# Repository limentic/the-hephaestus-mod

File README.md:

# The Hephaestus Mod

## ⚠️ DISCLAIMER ⚠️
Magic Keyboard is a trademark of Apple Inc.\
Apple Magic Keyboard is a trademark of Apple Inc.\
Touch ID is a trademark of Apple Inc.\
This project is not affiliated with Apple Inc. in any way.

The Hephaestus Mod is an independent project created by hardware enthusiasts. It is not endorsed, sponsored, ore supported by Apple Inc. Use this project at your own risk. Modifying your Magic Keyboard WILL void any warranty provided by Apple Inc.

## Introduction
The Hephaestus Mod is an open-source hardware modification for the Apple Magic Keyboard. This project aims create a mechanical keyboard using the Apple Magic Keyboard as a base.

## Getting Started
The Hephaestus Mod project is organized into the following directories:
- `ECAD-files/` - Contains the KiCad project files for the Hephaestus Mod.
    In this directory, you will find the following subdirectories:
    - `dev-board/` - Contains the KiCad project files for the development board. This board was used to test out if the reverse engineered keyboard matrix was correct.
    It can also be repurposed as a breakout board for the matrix connector. \
    **Be careful!** The revision 1.0 of the board contains errors for the 9, TAB and Option Right keys. I will make another revision of the dev board when I have time.
    - `prod-board/` - Contains the KiCad project files for the production board. This board is the version of the Hephaestus Mod that is intended to be used. \
    **Be careful!** For the moment this board is still not tested. It is still in manufacturing. I will update this README when I have tested it and confirmed that it works.
    - `touch-id-ribbon` - Contains the KiCad project files for the Touch ID ribbon cable. This cable is used to connect the Touch ID connector on the Apple motherboard to the production board.
- `MCAD-files/` - Contains the .STEP files of the Hephaestus Mod.
    - `hephaestus-case.step` - The case for the Hephaestus Mod.
    - `hephaestus-main-board.step` - The 3D model of the production board.
    - `magic-keyboard-battery.step` - The 3D model of the Magic Keyboard battery.
    - `magic-keyboard-motherboard.step` - The 3D model of the Magic Keyboard motherboard.

## Presumed Keyboard Matrices
You can check the presumed keyboard matrices below :
- [AZERTY Keyboard Matrix](./matrices/AZERTY.md)

## Build Instructions
🚧 **This section will be updated with instructions on how to get started with the Hephaestus Mod when the project is considered done.** 🚧

## License
This project is licensed under the CERN-OHL-S. See the [LICENSE](LICENSE) file for details.

## Contributing
We welcome contributions! Please read our [contributing guidelines](CONTRIBUTING.md) for more information on how to get involved.

## Contact
For questions, issues, or suggestions, please open an issue on our [GitHub repository](https://github.com/limentic/the-hephaestus-mod).

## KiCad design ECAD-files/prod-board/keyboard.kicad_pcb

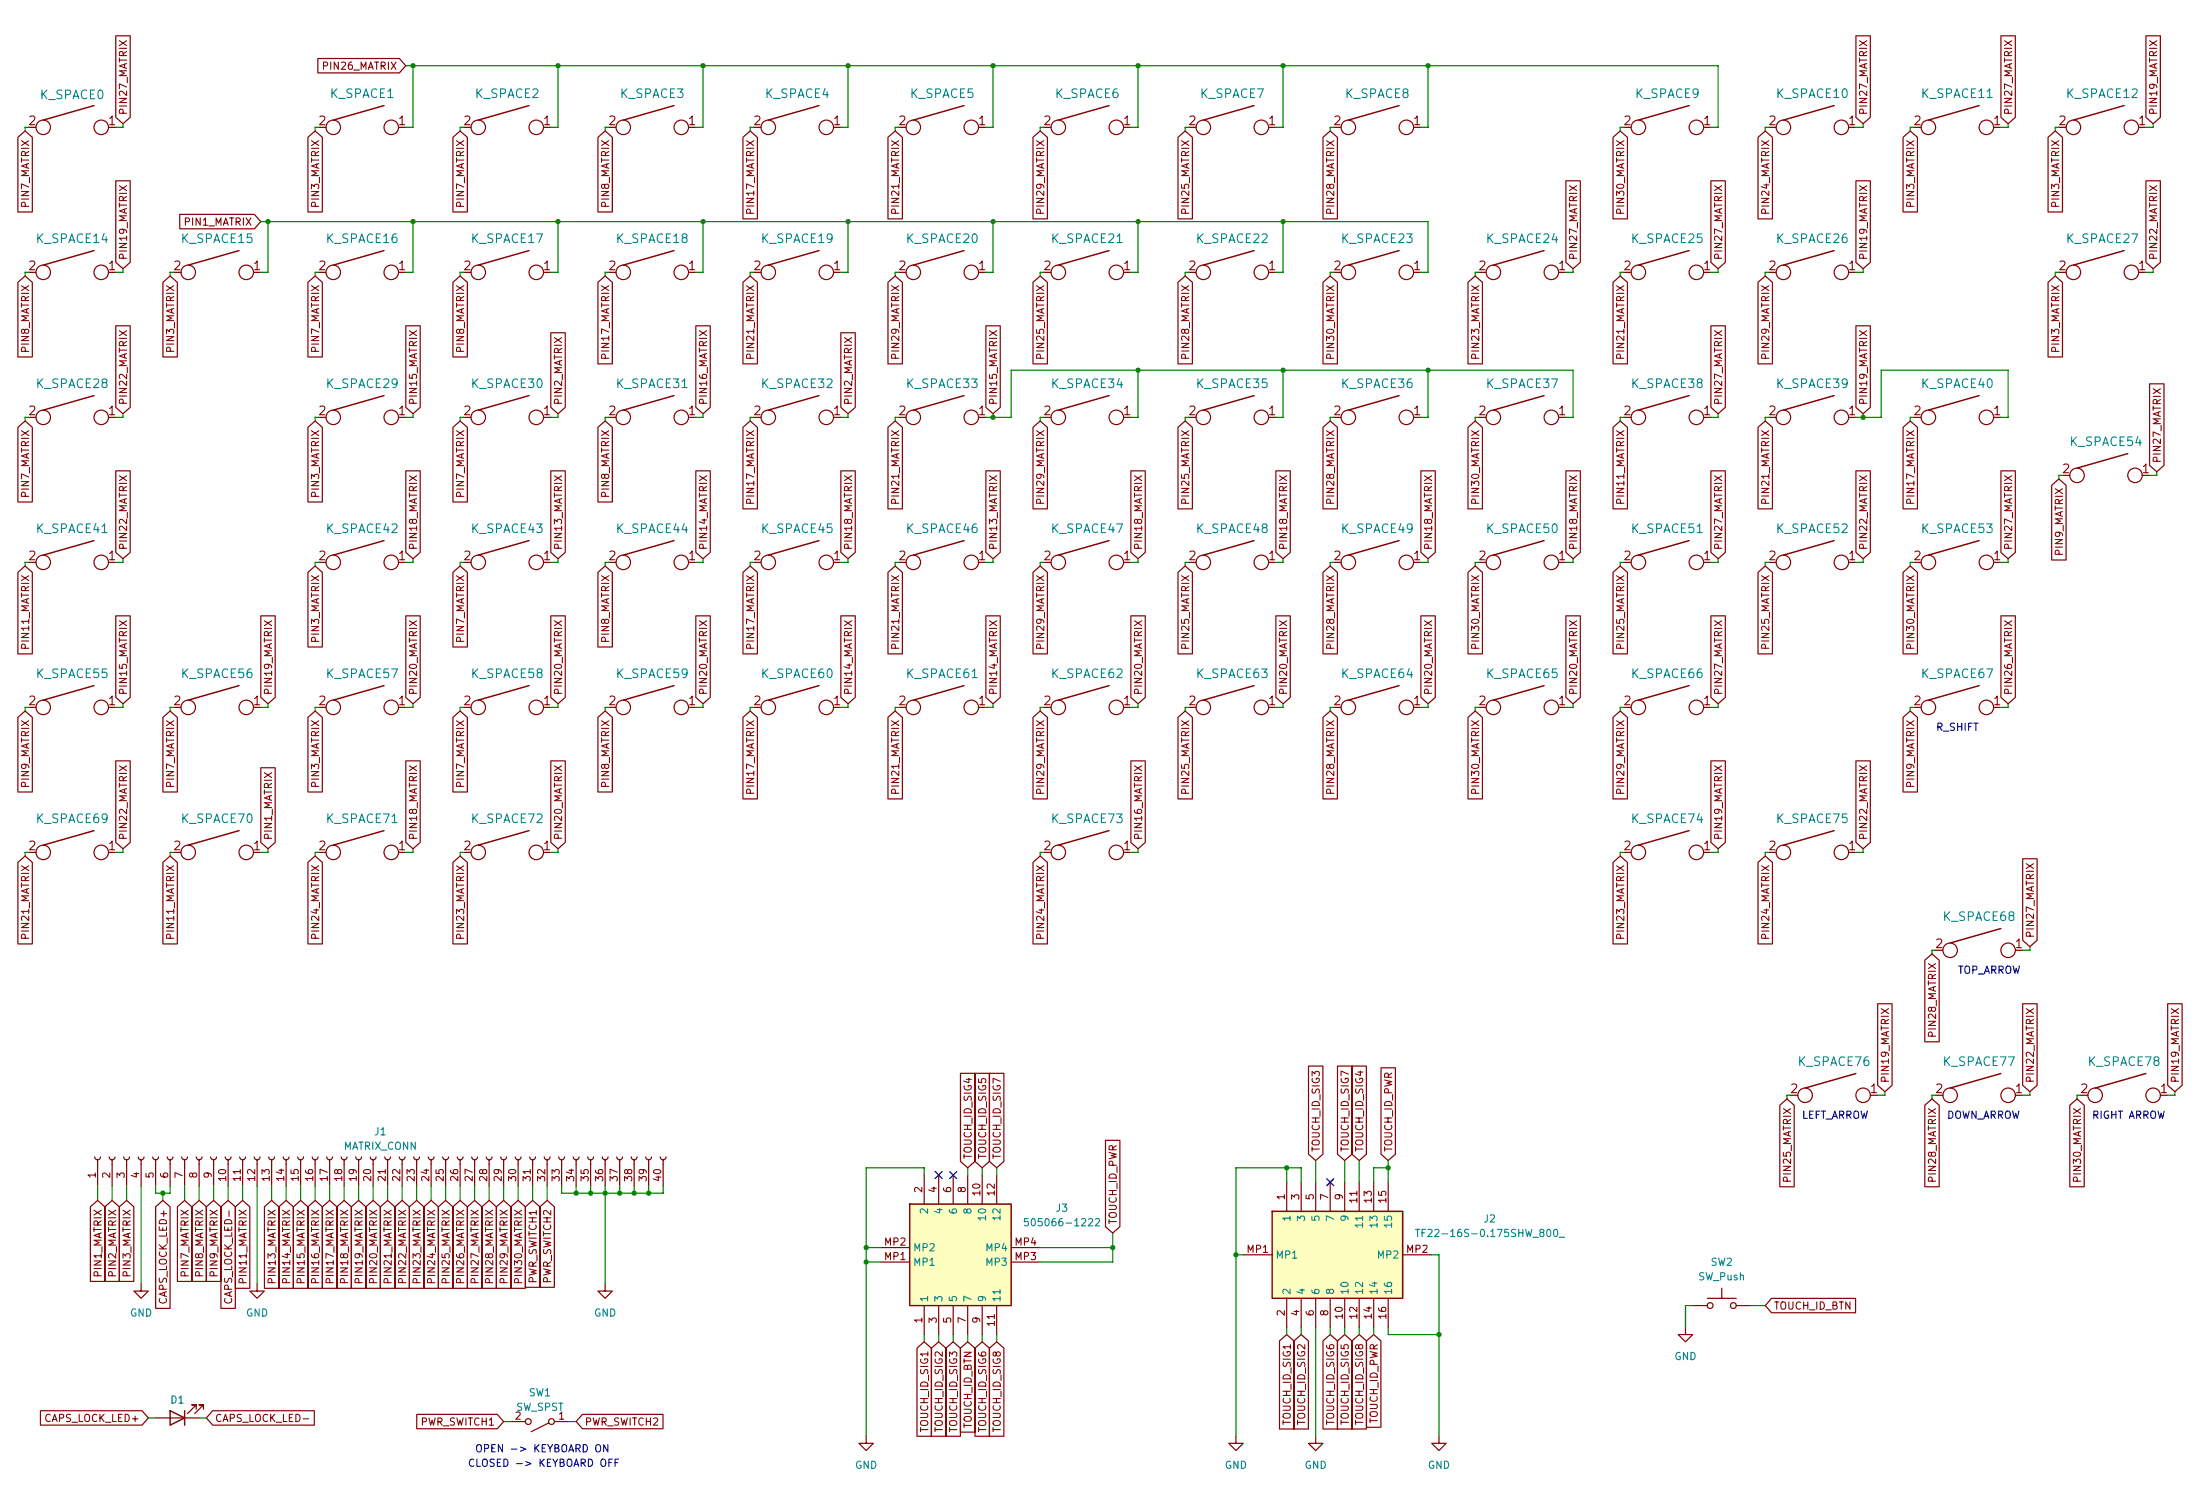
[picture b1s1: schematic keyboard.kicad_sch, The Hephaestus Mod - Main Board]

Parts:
D1: LED; LED_0805_2012Metric
J1: MATRIX_CONN; Hirose_FH12-40S-0.5SH_1x40-1MP_P0.50mm_Horizontal
J2: TF22-16S-0.175SHW_800_; TF2216S0175SHW800; Manufacturer_Part_Number TF22-16S-0.175SHW(800)
J3: 505066-1222; 5050661222; Mouser Part Number 538-505066-1222
K_SPACE0, K_SPACE1, K_SPACE2, K_SPACE3, K_SPACE4, K_SPACE5, K_SPACE6, K_SPACE7, K_SPACE8, K_SPACE9, K_SPACE10, K_SPACE11, K_SPACE12, K_SPACE14, K_SPACE15, K_SPACE16, K_SPACE17, K_SPACE18, K_SPACE19, K_SPACE20, K_SPACE21, K_SPACE22, K_SPACE23, K_SPACE24, K_SPACE25, K_SPACE26, K_SPACE29, K_SPACE30, K_SPACE31, K_SPACE32, K_SPACE33, K_SPACE34, K_SPACE35, K_SPACE36, K_SPACE37, K_SPACE38, K_SPACE39, K_SPACE40, K_SPACE42, K_SPACE43, K_SPACE44, K_SPACE45, K_SPACE46, K_SPACE47, K_SPACE48, K_SPACE49, K_SPACE50, K_SPACE51, K_SPACE52, K_SPACE53, K_SPACE56, K_SPACE57, K_SPACE58, K_SPACE59, K_SPACE60, K_SPACE61, K_SPACE62, K_SPACE63, K_SPACE64, K_SPACE65, K_SPACE66, K_SPACE68, K_SPACE69, K_SPACE70, K_SPACE71, K_SPACE75, K_SPACE76, K_SPACE77, K_SPACE78: KEYSW; MX-1U-NoLED
K_SPACE27: KEYSW; MX-2U-NoLED
K_SPACE28, K_SPACE67: KEYSW; MX-1.5U-NoLED
K_SPACE41: KEYSW; MX-1.75U-NoLED
K_SPACE54: KEYSW; MX-ISO-NoLED
K_SPACE55, K_SPACE72, K_SPACE74: KEYSW; MX-1.25U-NoLED
K_SPACE73: KEYSW; MX-6.25U-NoLED
SW1: SW_SPST; Molex_PicoBlade_53261-0271_1x02-1MP_P1.25mm_Horizontal
SW2: SW_Push; SW_SPST_PTS645

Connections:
CAPS_LOCK_LED+: D1.2 (A), J1.5, J1.6
CAPS_LOCK_LED-: D1.1 (K), J1.10
GND: J1.4, J1.12, J1.33, J1.34, J1.35, J1.36, J1.37, J1.38, J1.39, J1.40, J2.1, J2.3, J2.6, J2.16, J2.MP1, J2.MP2, J3.2, J3.MP1, J3.MP2, SW2.1
PIN1_MATRIX: J1.1, K_SPACE15.1, K_SPACE16.1, K_SPACE17.1, K_SPACE18.1, K_SPACE19.1, K_SPACE20.1, K_SPACE21.1, K_SPACE22.1, K_SPACE23.1, K_SPACE70.1
PIN2_MATRIX: J1.2, K_SPACE30.1, K_SPACE32.1
PIN3_MATRIX: J1.3, K_SPACE1.2, K_SPACE11.2, K_SPACE12.2, K_SPACE15.2, K_SPACE27.2, K_SPACE29.2, K_SPACE42.2, K_SPACE57.2
PIN7_MATRIX: J1.7, K_SPACE0.2, K_SPACE2.2, K_SPACE16.2, K_SPACE28.2, K_SPACE30.2, K_SPACE43.2, K_SPACE56.2, K_SPACE58.2
PIN8_MATRIX: J1.8, K_SPACE3.2, K_SPACE14.2, K_SPACE17.2, K_SPACE31.2, K_SPACE44.2, K_SPACE59.2
PIN9_MATRIX: J1.9, K_SPACE54.2, K_SPACE55.2, K_SPACE67.2
PIN11_MATRIX: J1.11, K_SPACE38.2, K_SPACE41.2, K_SPACE70.2
PIN13_MATRIX: J1.13, K_SPACE43.1, K_SPACE46.1
PIN14_MATRIX: J1.14, K_SPACE44.1, K_SPACE60.1, K_SPACE61.1
PIN15_MATRIX: J1.15, K_SPACE29.1, K_SPACE33.1, K_SPACE34.1, K_SPACE35.1, K_SPACE36.1, K_SPACE37.1, K_SPACE55.1
PIN16_MATRIX: J1.16, K_SPACE31.1, K_SPACE73.1
PIN17_MATRIX: J1.17, K_SPACE4.2, K_SPACE18.2, K_SPACE32.2, K_SPACE40.2, K_SPACE45.2, K_SPACE60.2
PIN18_MATRIX: J1.18, K_SPACE42.1, K_SPACE45.1, K_SPACE47.1, K_SPACE48.1, K_SPACE49.1, K_SPACE50.1, K_SPACE71.1
PIN19_MATRIX: J1.19, K_SPACE12.1, K_SPACE14.1, K_SPACE26.1, K_SPACE39.1, K_SPACE40.1, K_SPACE56.1, K_SPACE74.1, K_SPACE76.1, K_SPACE78.1
PIN20_MATRIX: J1.20, K_SPACE57.1, K_SPACE58.1, K_SPACE59.1, K_SPACE62.1, K_SPACE63.1, K_SPACE64.1, K_SPACE65.1, K_SPACE72.1
PIN21_MATRIX: J1.21, K_SPACE5.2, K_SPACE19.2, K_SPACE25.2, K_SPACE33.2, K_SPACE39.2, K_SPACE46.2, K_SPACE61.2, K_SPACE69.2
PIN22_MATRIX: J1.22, K_SPACE27.1, K_SPACE28.1, K_SPACE41.1, K_SPACE52.1, K_SPACE69.1, K_SPACE75.1, K_SPACE77.1
PIN23_MATRIX: J1.23, K_SPACE24.2, K_SPACE72.2, K_SPACE74.2
PIN24_MATRIX: J1.24, K_SPACE10.2, K_SPACE71.2, K_SPACE73.2, K_SPACE75.2
PIN25_MATRIX: J1.25, K_SPACE7.2, K_SPACE21.2, K_SPACE35.2, K_SPACE48.2, K_SPACE51.2, K_SPACE52.2, K_SPACE63.2, K_SPACE76.2
PIN26_MATRIX: J1.26, K_SPACE1.1, K_SPACE2.1, K_SPACE3.1, K_SPACE4.1, K_SPACE5.1, K_SPACE6.1, K_SPACE7.1, K_SPACE8.1, K_SPACE9.1, K_SPACE67.1
PIN27_MATRIX: J1.27, K_SPACE0.1, K_SPACE10.1, K_SPACE11.1, K_SPACE24.1, K_SPACE25.1, K_SPACE38.1, K_SPACE51.1, K_SPACE53.1, K_SPACE54.1, K_SPACE66.1, K_SPACE68.1
PIN28_MATRIX: J1.28, K_SPACE8.2, K_SPACE22.2, K_SPACE36.2, K_SPACE49.2, K_SPACE64.2, K_SPACE68.2, K_SPACE77.2
PIN29_MATRIX: J1.29, K_SPACE6.2, K_SPACE20.2, K_SPACE26.2, K_SPACE34.2, K_SPACE47.2, K_SPACE62.2, K_SPACE66.2
PIN30_MATRIX: J1.30, K_SPACE9.2, K_SPACE23.2, K_SPACE37.2, K_SPACE50.2, K_SPACE53.2, K_SPACE65.2, K_SPACE78.2
PWR_SWITCH1: J1.31, SW1.2 (B)
PWR_SWITCH2: J1.32, SW1.1 (A)
TOUCH_ID_BTN: J3.7, SW2.2
TOUCH_ID_PWR: J2.13, J2.14, J2.15, J3.MP3, J3.MP4
TOUCH_ID_SIG1: J2.2, J3.1
TOUCH_ID_SIG2: J2.4, J3.3
TOUCH_ID_SIG3: J2.5, J3.5
TOUCH_ID_SIG4: J2.11, J3.8
TOUCH_ID_SIG5: J2.10, J3.10
TOUCH_ID_SIG6: J2.8, J3.9
TOUCH_ID_SIG7: J2.9, J3.12
TOUCH_ID_SIG8: J2.12, J3.11

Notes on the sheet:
R_SHIFT
DOWN_ARROW
TOP_ARROW
RIGHT ARROW
OPEN -> KEYBOARD ON
CLOSED -> KEYBOARD OFF
LEFT_ARROW

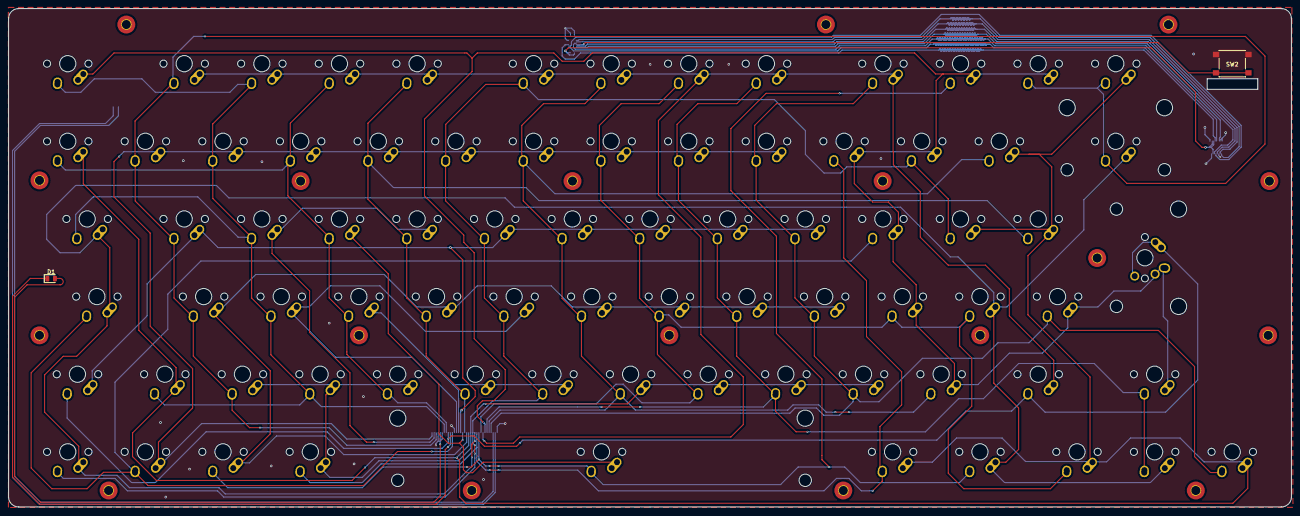
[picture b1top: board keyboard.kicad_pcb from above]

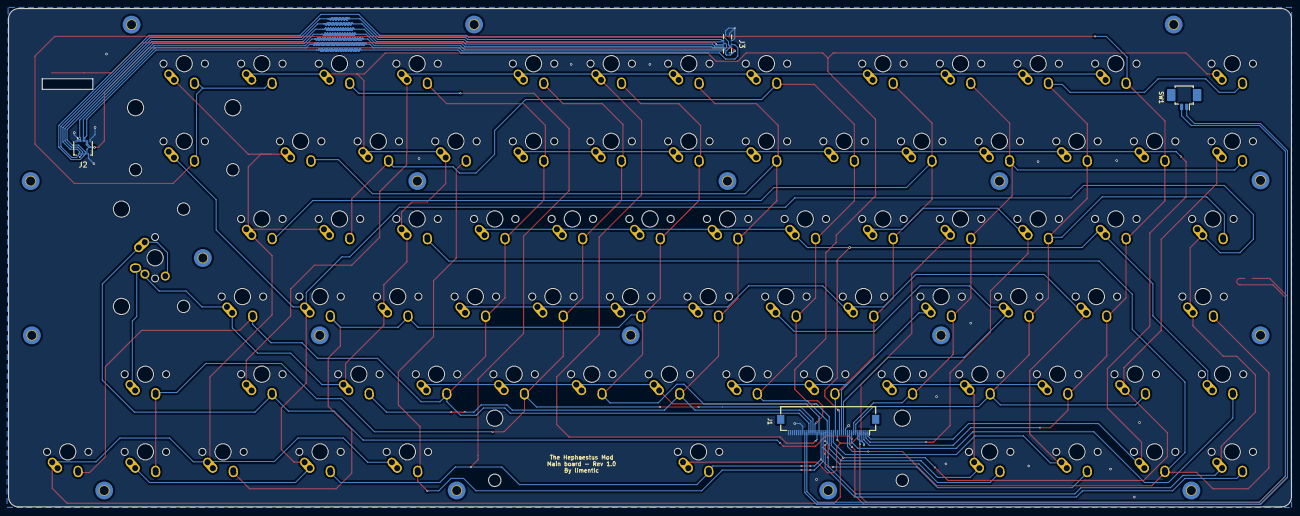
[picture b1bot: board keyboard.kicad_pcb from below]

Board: 2 copper layers, 314.8 x 122.3 mm, 84 parts (4 on the bottom side), 40 nets.

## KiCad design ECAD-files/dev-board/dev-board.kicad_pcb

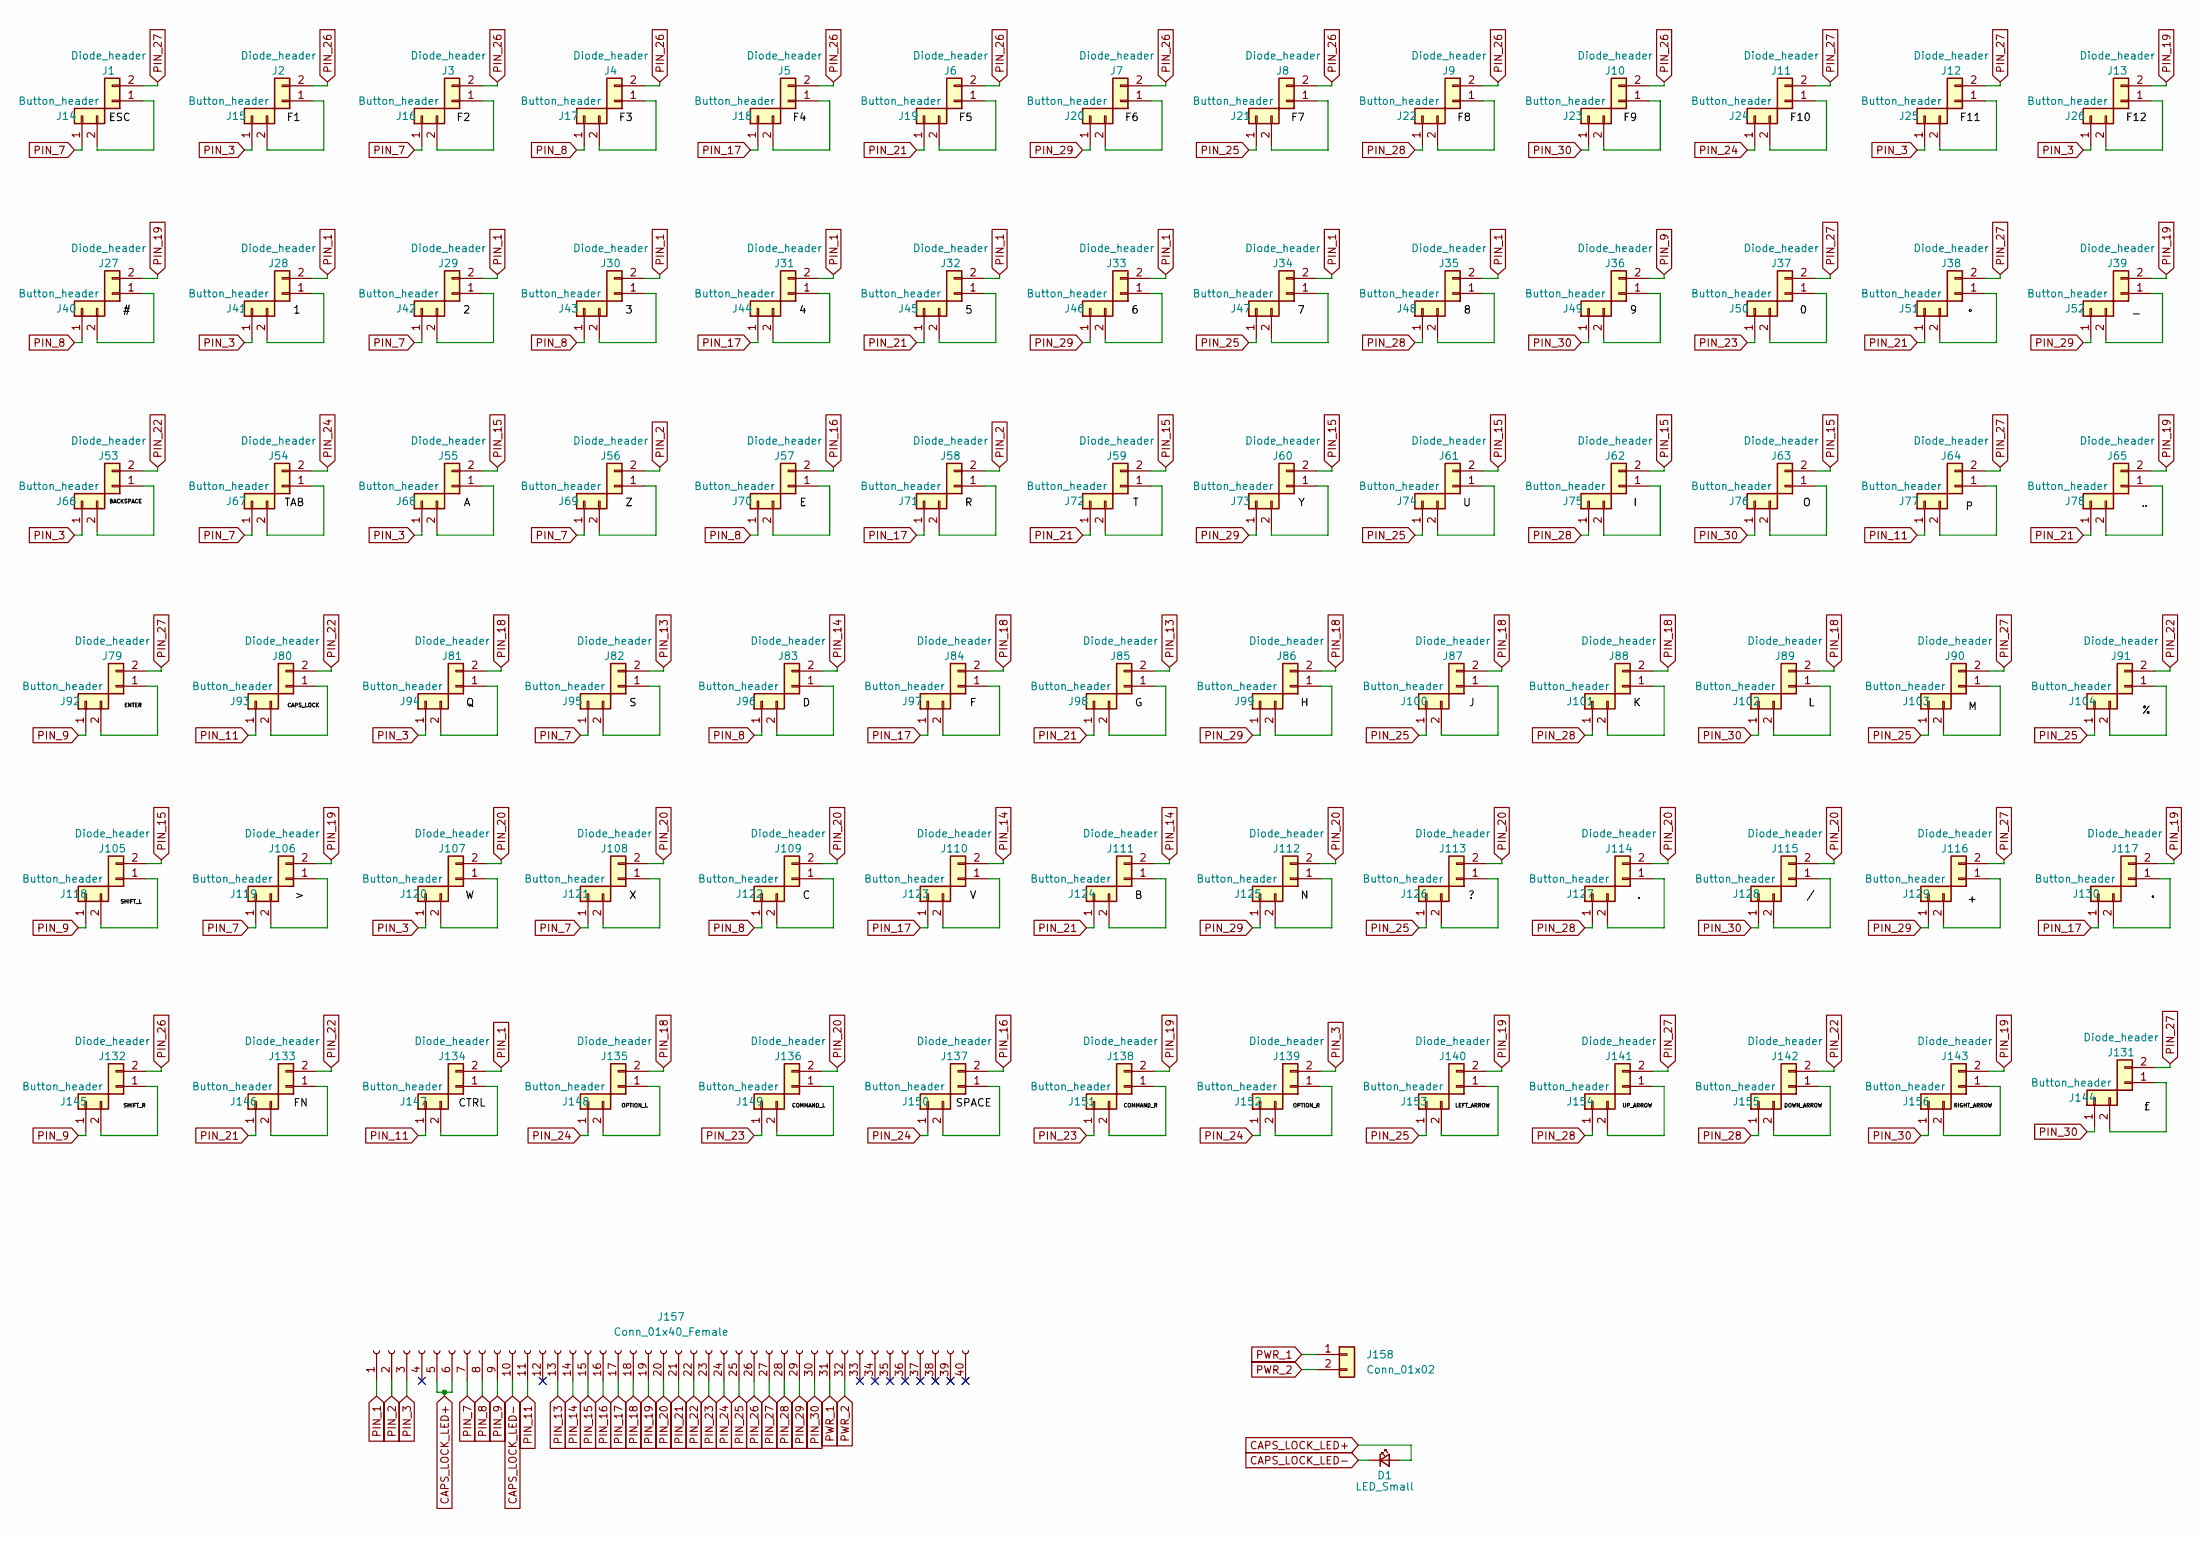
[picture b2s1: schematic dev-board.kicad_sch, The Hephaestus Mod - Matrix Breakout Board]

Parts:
D1: LED_Small; LED_0805_2012Metric
J1, J2, J3, J4, J5, J6, J7, J8, J9, J10, J11, J12, J13, J27, J28, J29, J30, J31, J32, J33, J34, J35, J36, J37, J38, J39, J53, J54, J55, J56, J57, J58, J59, J60, J61, J62, J63, J64, J65, J79, J80, J81, J82, J83, J84, J85, J86, J87, J88, J89, J90, J91, J105, J106, J107, J108, J109, J110, J111, J112, J113, J114, J115, J116, J117, J131, J132, J133, J134, J135, J136, J137, J138, J139, J140, J141, J142, J143: Diode_header; PinHeader_1x02_P2.54mm_Vertical
J14, J15, J16, J17, J18, J19, J20, J21, J22, J23, J24, J25, J26, J40, J41, J42, J43, J44, J45, J46, J47, J48, J49, J50, J51, J52, J66, J67, J68, J69, J70, J71, J72, J73, J74, J75, J76, J77, J78, J92, J93, J94, J95, J96, J97, J98, J99, J100, J101, J102, J103, J104, J118, J119, J120, J121, J122, J123, J124, J125, J126, J127, J128, J129, J130, J144, J145, J146, J147, J148, J149, J150, J151, J152, J153, J154, J155, J156: Button_header; PinHeader_1x02_P2.54mm_Vertical
J157: Conn_01x40_Female; Hirose_FH12-40S-0.5SH_1x40-1MP_P0.50mm_Horizontal
J158: Conn_01x02; PinHeader_1x02_P2.54mm_Vertical

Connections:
CAPS_LOCK_LED+: D1.2 (A), J157.5, J157.6
CAPS_LOCK_LED-: D1.1 (K), J157.10
unnamed: J1.1, J14.2
unnamed: J10.1, J23.2
unnamed: J11.1, J24.2
unnamed: J12.1, J25.2
unnamed: J13.1, J26.2
unnamed: J2.1, J15.2
unnamed: J3.1, J16.2
unnamed: J4.1, J17.2
unnamed: J5.1, J18.2
unnamed: J6.1, J19.2
unnamed: J7.1, J20.2
unnamed: J8.1, J21.2
unnamed: J9.1, J22.2
unnamed: J27.1, J40.2
unnamed: J28.1, J41.2
unnamed: J29.1, J42.2
unnamed: J30.1, J43.2
unnamed: J31.1, J44.2
unnamed: J32.1, J45.2
unnamed: J33.1, J46.2
unnamed: J34.1, J47.2
unnamed: J35.1, J48.2
unnamed: J36.1, J49.2
unnamed: J37.1, J50.2
unnamed: J38.1, J51.2
unnamed: J39.1, J52.2
unnamed: J53.1, J66.2
unnamed: J54.1, J67.2
unnamed: J55.1, J68.2
unnamed: J56.1, J69.2
unnamed: J57.1, J70.2
unnamed: J58.1, J71.2
unnamed: J59.1, J72.2
unnamed: J60.1, J73.2
unnamed: J61.1, J74.2
unnamed: J62.1, J75.2
unnamed: J63.1, J76.2
unnamed: J64.1, J77.2
unnamed: J65.1, J78.2
unnamed: J79.1, J92.2
unnamed: J80.1, J93.2
unnamed: J81.1, J94.2
unnamed: J82.1, J95.2
unnamed: J83.1, J96.2
unnamed: J84.1, J97.2
unnamed: J85.1, J98.2
unnamed: J86.1, J99.2
unnamed: J87.1, J100.2
unnamed: J88.1, J101.2
unnamed: J89.1, J102.2
unnamed: J90.1, J103.2
unnamed: J91.1, J104.2
unnamed: J105.1, J118.2
unnamed: J106.1, J119.2
unnamed: J107.1, J120.2
unnamed: J108.1, J121.2
unnamed: J109.1, J122.2
unnamed: J110.1, J123.2
unnamed: J111.1, J124.2
unnamed: J112.1, J125.2
unnamed: J113.1, J126.2
unnamed: J114.1, J127.2
unnamed: J115.1, J128.2
unnamed: J116.1, J129.2
unnamed: J117.1, J130.2
unnamed: J131.1, J144.2
unnamed: J132.1, J145.2
unnamed: J133.1, J146.2
unnamed: J134.1, J147.2
unnamed: J135.1, J148.2
unnamed: J136.1, J149.2
unnamed: J137.1, J150.2
unnamed: J138.1, J151.2
unnamed: J139.1, J152.2
unnamed: J140.1, J153.2
unnamed: J141.1, J154.2
unnamed: J142.1, J155.2
unnamed: J143.1, J156.2
PIN_1: J28.2, J29.2, J30.2, J31.2, J32.2, J33.2, J34.2, J35.2, J134.2, J157.1
PIN_2: J56.2, J58.2, J157.2
PIN_3: J15.1, J25.1, J26.1, J41.1, J66.1, J68.1, J94.1, J120.1, J139.2, J157.3
PIN_7: J14.1, J16.1, J42.1, J67.1, J69.1, J95.1, J119.1, J121.1, J157.7
PIN_8: J17.1, J40.1, J43.1, J70.1, J96.1, J122.1, J157.8
PIN_9: J36.2, J92.1, J118.1, J145.1, J157.9
PIN_11: J77.1, J93.1, J147.1, J157.11
PIN_13: J82.2, J85.2, J157.13
PIN_14: J83.2, J110.2, J111.2, J157.14
PIN_15: J55.2, J59.2, J60.2, J61.2, J62.2, J63.2, J105.2, J157.15
PIN_16: J57.2, J137.2, J157.16
PIN_17: J18.1, J44.1, J71.1, J97.1, J123.1, J130.1, J157.17
PIN_18: J81.2, J84.2, J86.2, J87.2, J88.2, J89.2, J135.2, J157.18
PIN_19: J13.2, J27.2, J39.2, J65.2, J106.2, J117.2, J138.2, J140.2, J143.2, J157.19
PIN_20: J107.2, J108.2, J109.2, J112.2, J113.2, J114.2, J115.2, J136.2, J157.20
PIN_21: J19.1, J45.1, J51.1, J72.1, J78.1, J98.1, J124.1, J146.1, J157.21
PIN_22: J53.2, J80.2, J91.2, J133.2, J142.2, J157.22
PIN_23: J50.1, J149.1, J151.1, J157.23
PIN_24: J24.1, J54.2, J148.1, J150.1, J152.1, J157.24
PIN_25: J21.1, J47.1, J74.1, J100.1, J103.1, J104.1, J126.1, J153.1, J157.25
PIN_26: J2.2, J3.2, J4.2, J5.2, J6.2, J7.2, J8.2, J9.2, J10.2, J132.2, J157.26
PIN_27: J1.2, J11.2, J12.2, J37.2, J38.2, J64.2, J79.2, J90.2, J116.2, J131.2, J141.2, J157.27
PIN_28: J22.1, J48.1, J75.1, J101.1, J127.1, J154.1, J155.1, J157.28
PIN_29: J20.1, J46.1, J52.1, J73.1, J99.1, J125.1, J129.1, J157.29
PIN_30: J23.1, J49.1, J76.1, J102.1, J128.1, J144.1, J156.1, J157.30
PWR_1: J157.31, J158.1
PWR_2: J157.32, J158.2

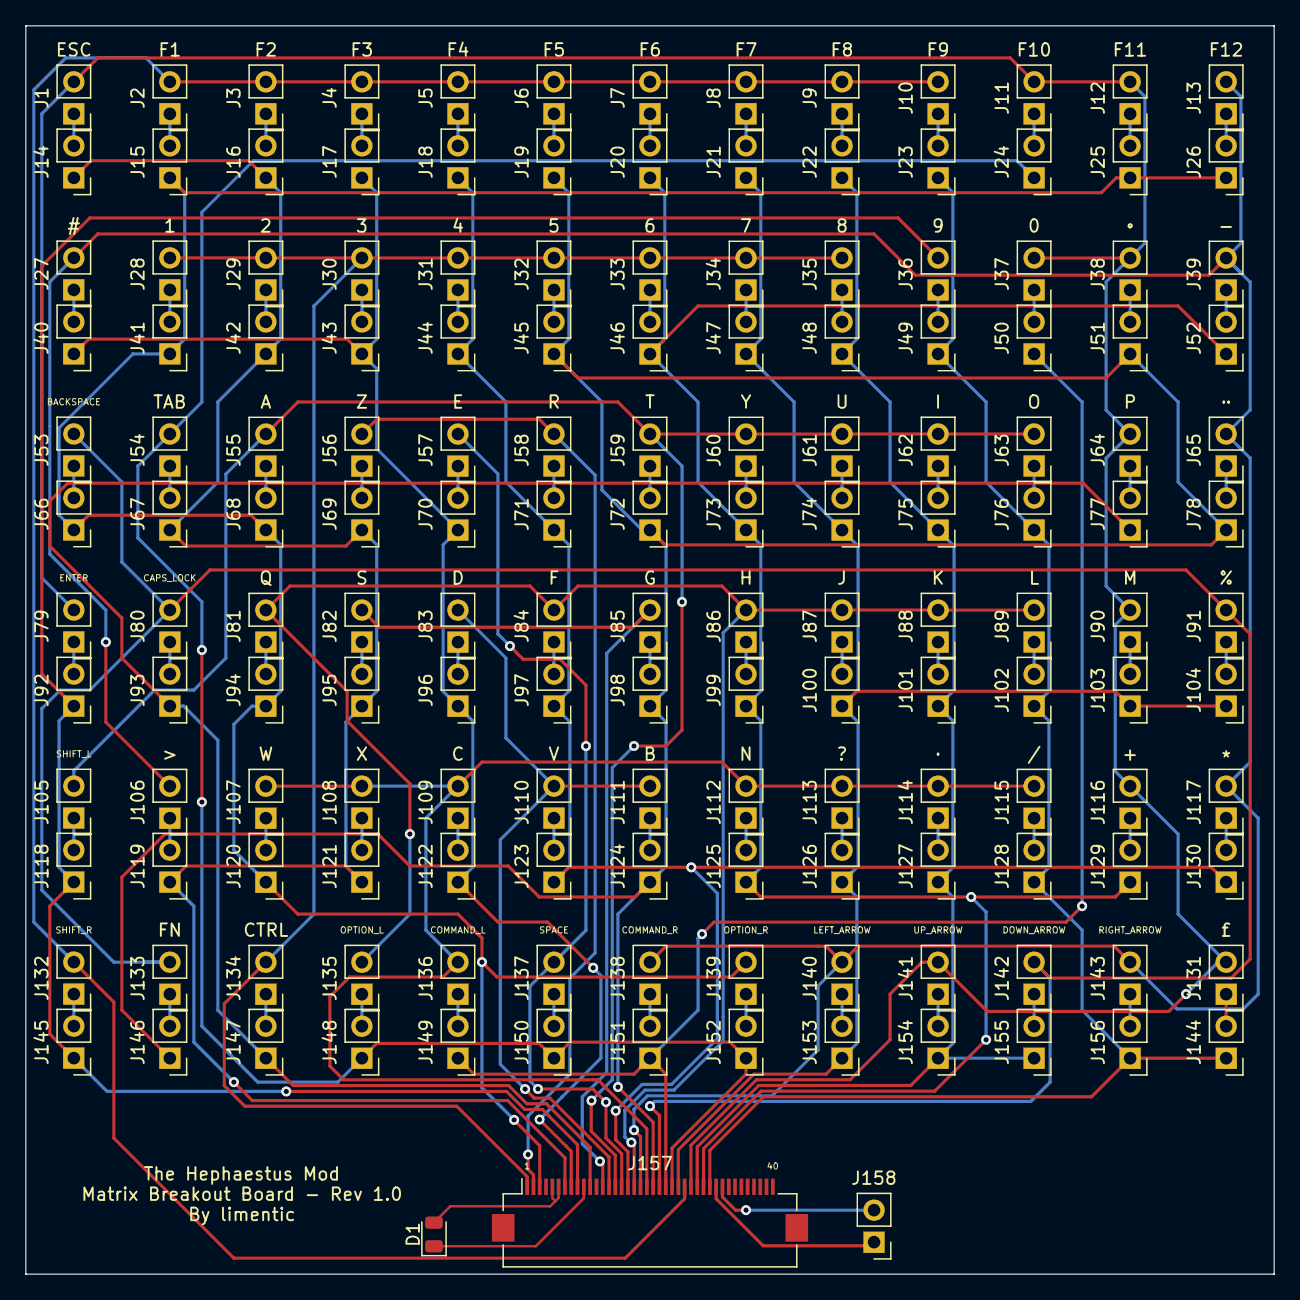
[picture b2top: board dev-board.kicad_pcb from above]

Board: 2 copper layers, 99.1 x 99.1 mm, 159 parts (0 on the bottom side), 107 nets.

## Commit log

2024-09-13 Added keycap files.
2024-10-04 Removed wrong size .stl and replaced them with .step files.
